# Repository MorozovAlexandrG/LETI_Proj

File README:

Realisation plan

Логика работы:
Спим пока пользователь не нажмёт на кнопку
После нажатия, выходим из deep sleep, подавая питание на ad8232
Мгновенно начинаем снимать сигнал, при условии что электроды подключены и все модули готовы(в коде)
Точки сохраняем в RAM
После набора некоторого количества точек пишем в microsd

План реализации:
1) Проверка deep sleep(С кнопкой)
2) Проверка сьёма данных ad8232
3) Проверка записи данных в microsd
4) Проверка чтения данных из microsd
5) Проверка записи данных ad8232 microsd
6) Реализация проверки работы ad8232 при включении устройства
7) Проверка подключения к wifi
8) Проверка отправки данных на сервер
9) Логирование данных

hardware

1) Используемые компоненты:
xiao esp32 c3
micro sd module
0,96 oled
button
ad8232

2) Метод изготовления печатной платы: 
ЛУТ

3) Возможные дополнения в случае кривого сигнала:
Проводы экранированные

Model
Корпус прямоугольной формы freecad

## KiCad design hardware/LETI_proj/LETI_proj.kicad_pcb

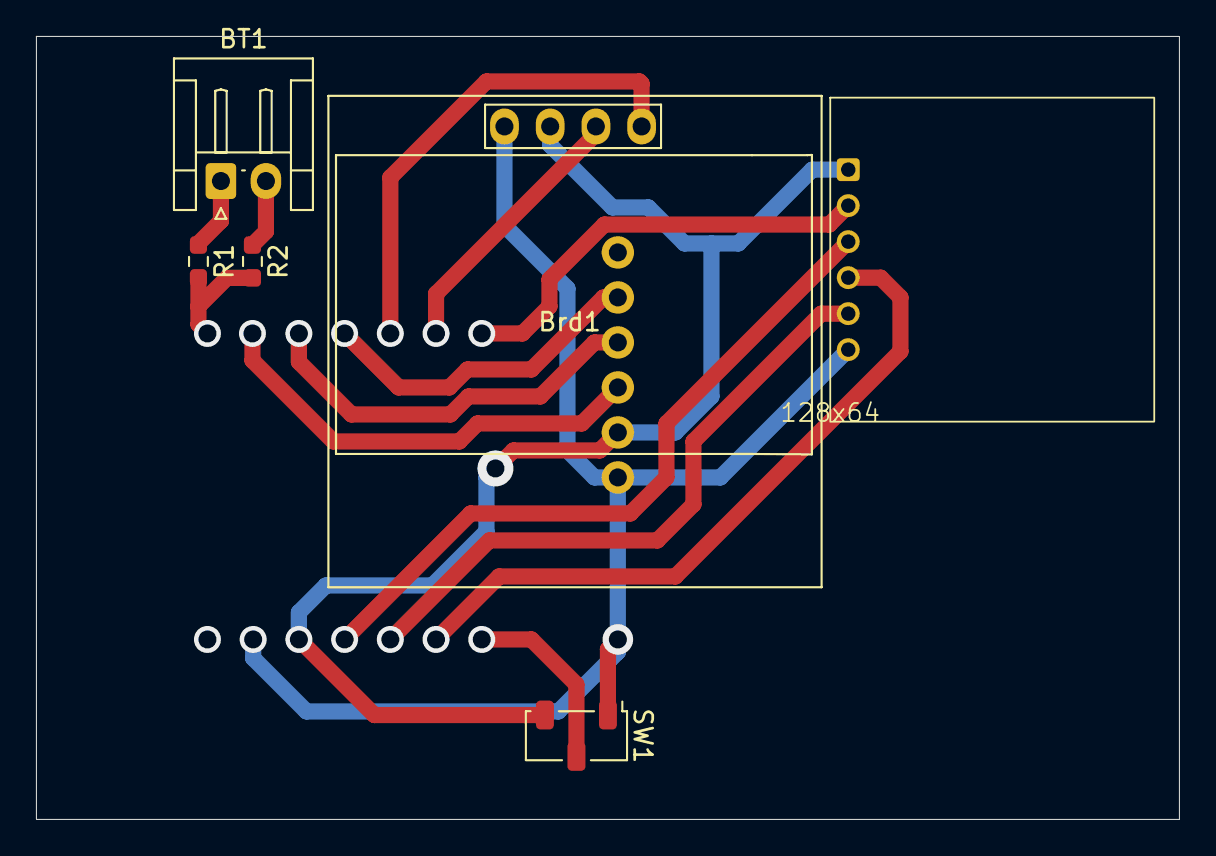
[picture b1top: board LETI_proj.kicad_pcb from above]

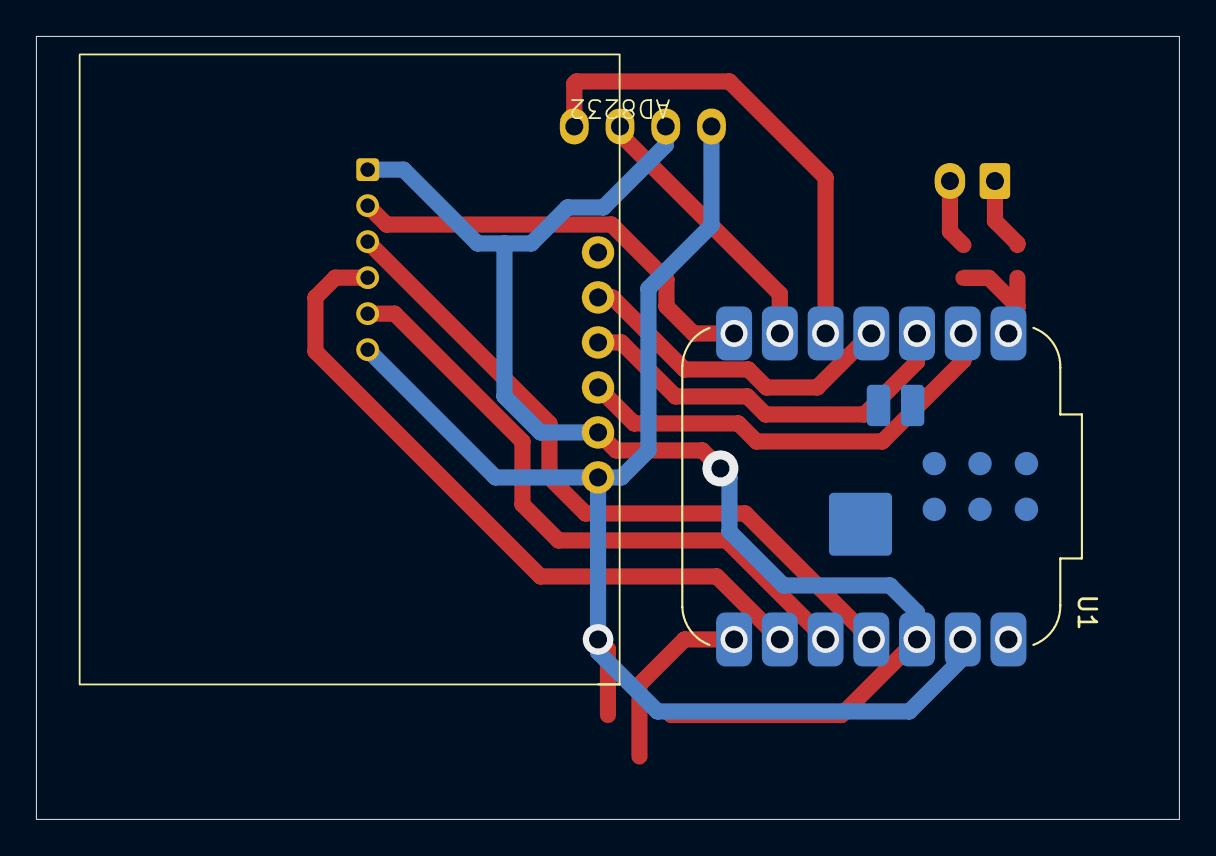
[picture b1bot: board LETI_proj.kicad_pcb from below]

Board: 2 copper layers, 63.5 x 43.5 mm, 8 parts (2 on the bottom side), 15 nets.

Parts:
128x64: microsd
AD8232: ad8232
BT1: Battery; JST_EH_S2B-EH_1x02_P2.50mm_Horizontal
Brd1: SSD1306; 128x64OLED
R1, R2: R_0603_1608Metric_Pad0.98x0.95mm_HandSolder
SW1: SW_Nidec_CAS-120A1; Nidec_Copal_CAS-120A
U1: XIAO ESP32C3; MCU_Seeed_ESP32C3

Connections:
/3V3: 128x64.1 (3V3), AD8232.2 (3V3), Brd1.2 (VCC), SW1.3 (A), U1.12 (VCC_3V3)
/B+: BT1.1 (+), R1.1, U1.16 (Batt+)
/B-: BT1.2 (-), R2.1, U1.17 (Batt-)
/CS: 128x64.2 (cs), U1.7 (D6)
/D0: R1.2, R2.2, U1.1 (D0)
/GND: 128x64.6 (gnd), AD8232.1 (GND), Brd1.1 (GND), SW1.1 (C), U1.13 (GND)
/LO+: AD8232.5 (LO+), U1.4 (D3)
/LO-: AD8232.4 (LO-), U1.3 (D2)
/MISO: 128x64.5 (miso), U1.10 (D9)
/MOSI: 128x64.3 (mosi), U1.11 (D10)
/SCK: 128x64.4 (sck), U1.9 (D8)
/ad_output: AD8232.3 (OUTPUT), U1.2 (D1)
/scl: Brd1.3 (SCL), U1.6 (D5)
/sda: Brd1.4 (SDA), U1.5 (D4)
unnamed: SW1.2 (B), U1.8 (D7)
